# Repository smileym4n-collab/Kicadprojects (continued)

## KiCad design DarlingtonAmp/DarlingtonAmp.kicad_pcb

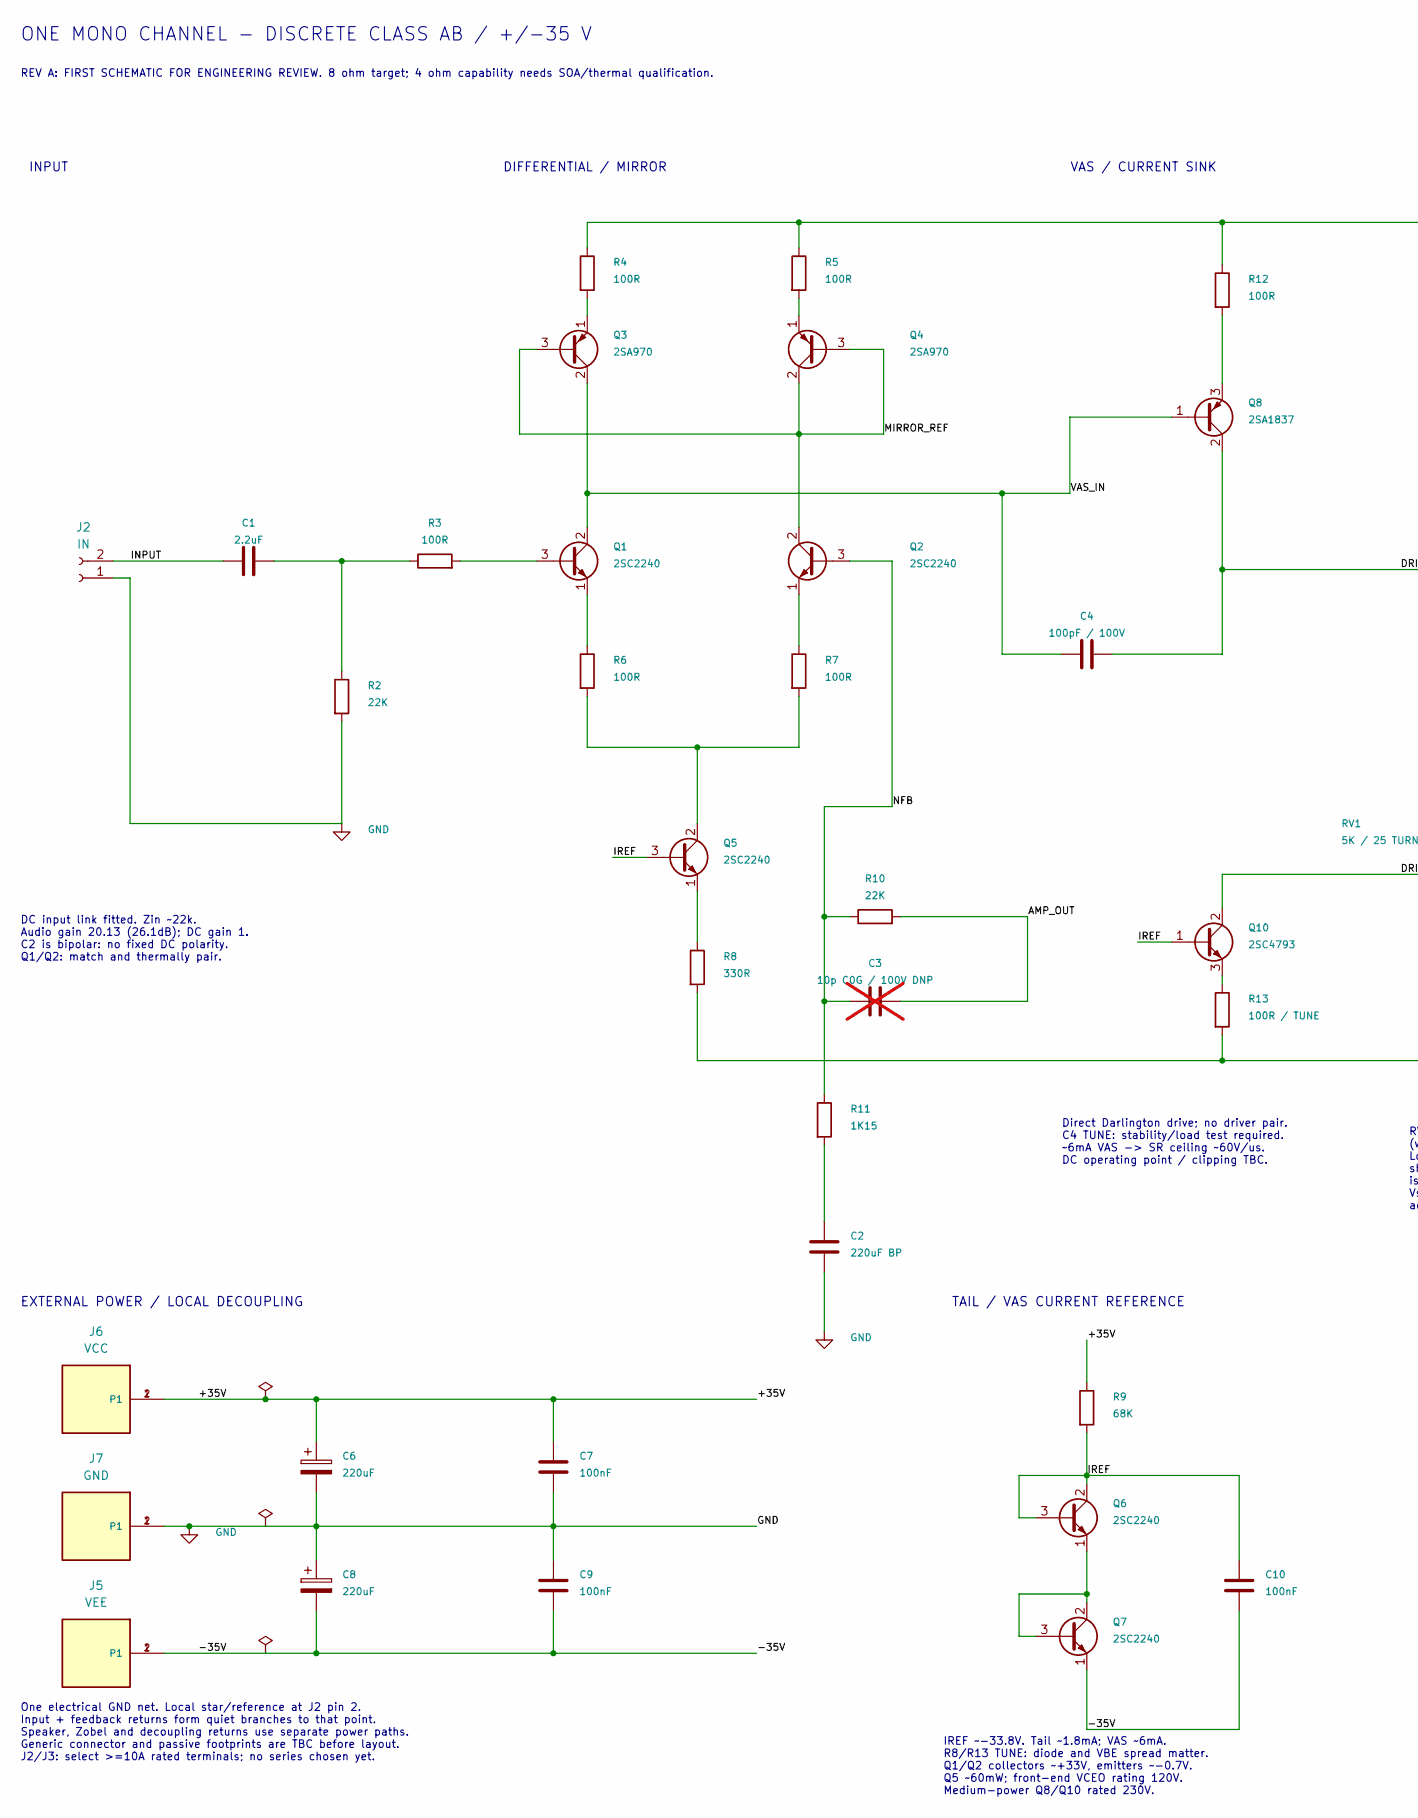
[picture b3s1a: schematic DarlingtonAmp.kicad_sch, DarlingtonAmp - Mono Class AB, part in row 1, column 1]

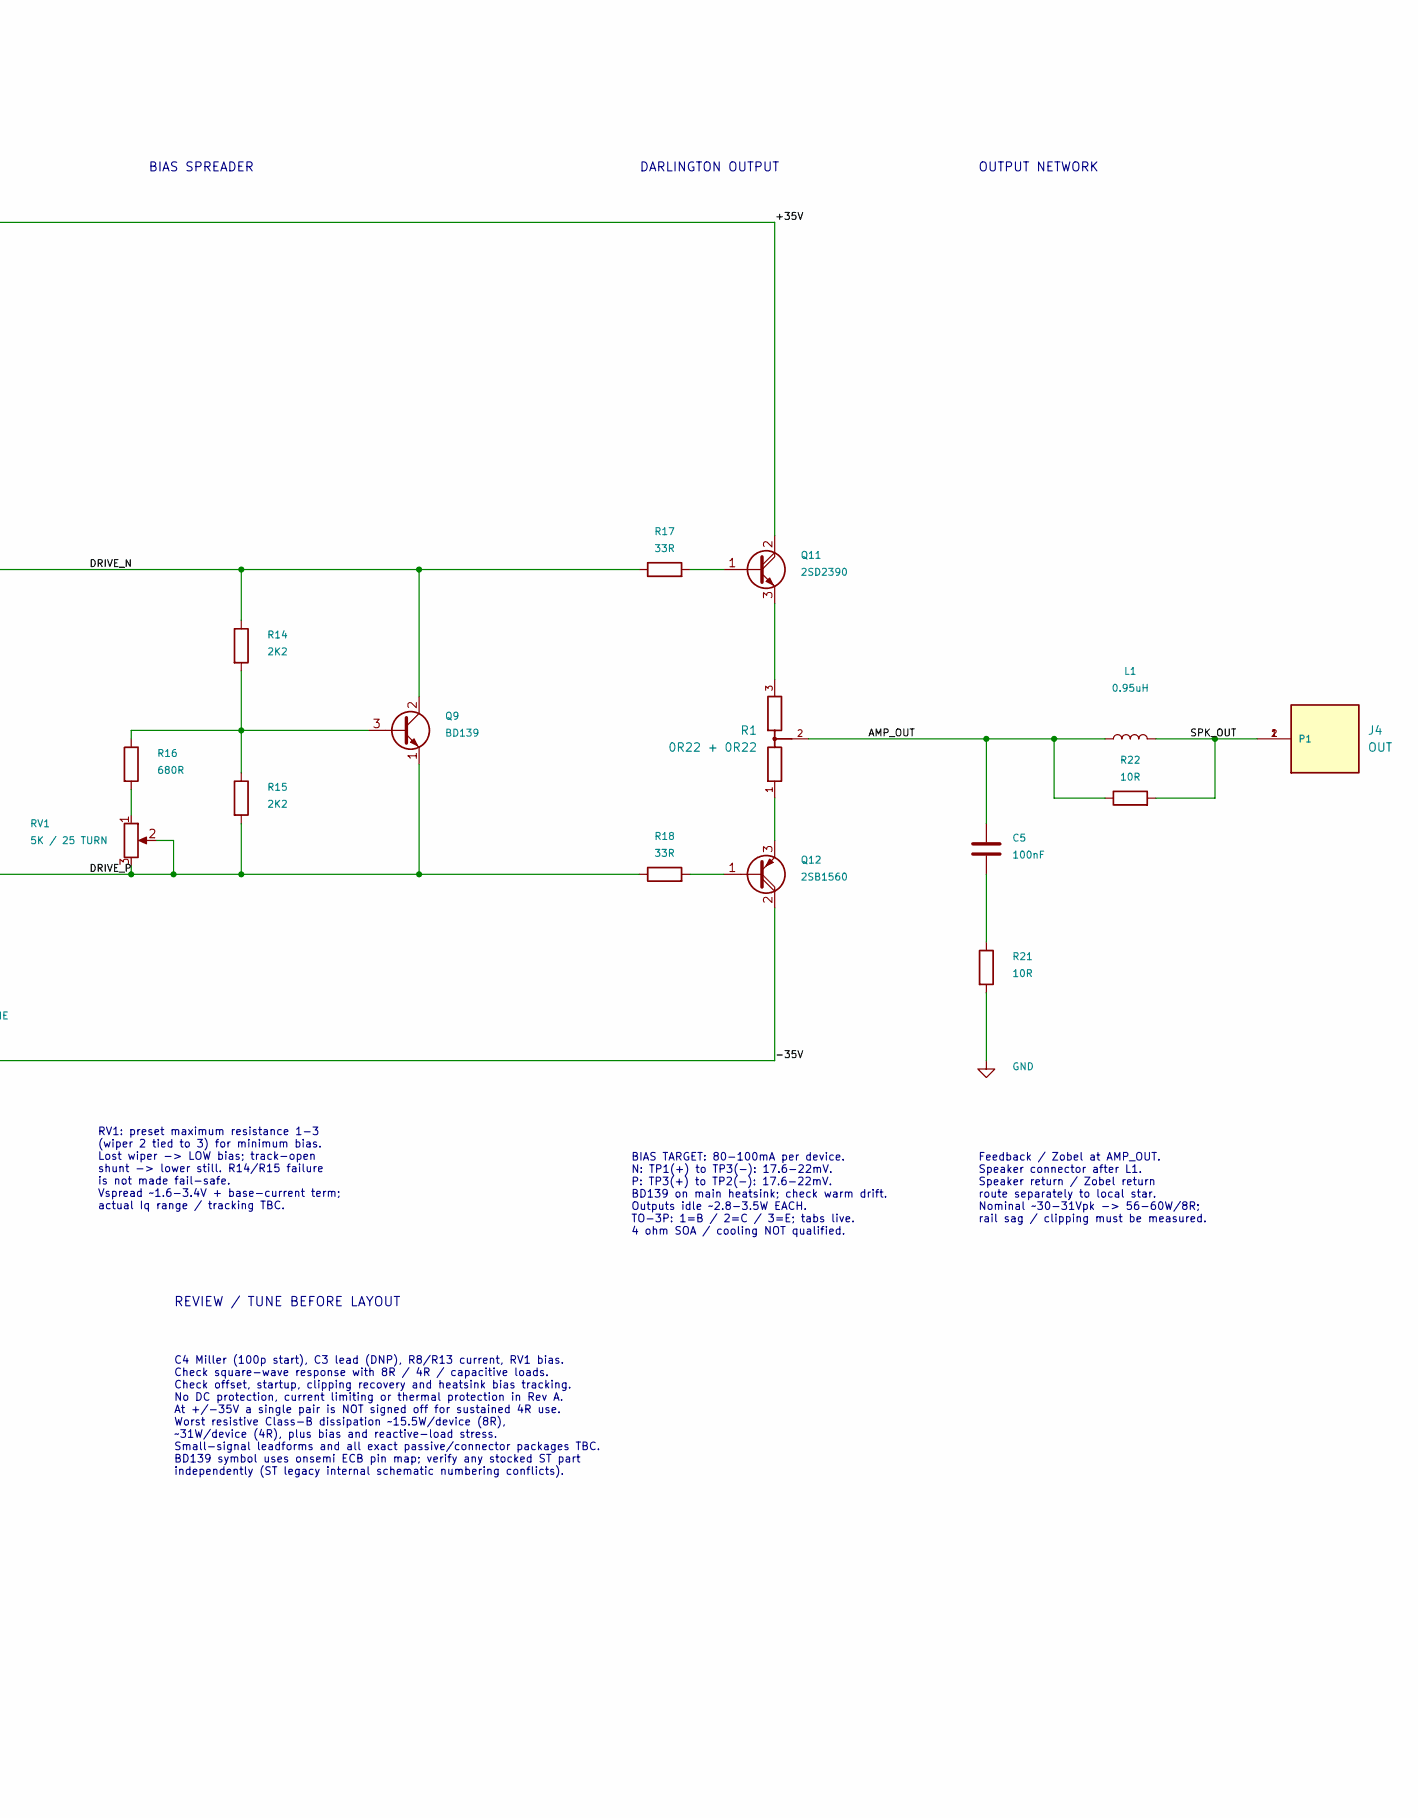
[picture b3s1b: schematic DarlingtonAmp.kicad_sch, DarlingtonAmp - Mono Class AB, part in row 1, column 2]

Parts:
C1: 2.2uF; C_Rect_L7.2mm_W7.2mm_P5.00mm_FKS2_FKP2_MKS2_MKP2
C2: 220uF BP; C_Radial_D16.0mm_H25.0mm_P7.50mm
C3: 10p C0G / 100V DNP; C_Disc_D4.3mm_W1.9mm_P5.00mm; not fitted
C4: 100pF / 100V; C_0805_2012Metric_Pad1.18x1.45mm_HandSolder
C5, C7, C9, C10: 100nF; C_Rect_L7.0mm_W2.5mm_P5.00mm
C6, C8: 220uF; CP_Radial_D10.0mm_P5.00mm
J2: IN; JST_XH_B2B-XH-A_1x02_P2.50mm_Vertical
J4: OUT; TE_62409-1; PART_DESCRIPTION CONN QC TAB 0.250 SOLDER
J5: VEE; TE_62409-1; PART_DESCRIPTION CONN QC TAB 0.250 SOLDER
J6: VCC; TE_62409-1; PART_DESCRIPTION CONN QC TAB 0.250 SOLDER
J7: GND; TE_62409-1; PART_DESCRIPTION CONN QC TAB 0.250 SOLDER
L1: 0.95uH; L_Yamaha_L505_15x15mm_P12mm
Q1, Q2, Q5, Q6, Q7: 2SC2240; TO-92_Inline_Wide
Q3, Q4: 2SA970; TO-92_Inline_Wide
Q8: 2SA1837; TO-220-3_Vertical
Q9: BD139; TO-126-3_Horizontal_TabDown
Q10: 2SC4793; TO-220-3_Vertical
Q11: 2SD2390; TO-3PB-3_Horizontal_TabDown
Q12: 2SB1560; TO-3PB-3_Horizontal_TabDown
R1: 0R22 + 0R22; R_Dual_Power_L31_W5_H18_P10
R2, R10: 22K; R_Axial_DIN0207_L6.3mm_D2.5mm_P7.62mm_Horizontal
R3, R4, R5, R6, R7, R12: 100R; R_Axial_DIN0207_L6.3mm_D2.5mm_P7.62mm_Horizontal
R8: 330R; R_Axial_DIN0207_L6.3mm_D2.5mm_P7.62mm_Horizontal
R9: 68K; R_Axial_DIN0207_L6.3mm_D2.5mm_P7.62mm_Horizontal
R11: 1K15; R_Axial_DIN0207_L6.3mm_D2.5mm_P7.62mm_Horizontal
R13: 100R / TUNE; R_Axial_DIN0207_L6.3mm_D2.5mm_P7.62mm_Horizontal
R14, R15: 2K2; R_Axial_DIN0207_L6.3mm_D2.5mm_P7.62mm_Horizontal
R16: 680R; R_Axial_DIN0207_L6.3mm_D2.5mm_P7.62mm_Horizontal
R17, R18: 33R; R_Axial_DIN0207_L6.3mm_D2.5mm_P7.62mm_Horizontal
R21, R22: 10R; R_Axial_DIN0414_L11.9mm_D4.5mm_P15.24mm_Horizontal
RV1: 5K / 25 TURN; Potentiometer_Bourns_3296W_Vertical

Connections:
/+35V: C6.1, C7.1, J6.1, J6.2 (P1), Q11.2 (C), R4.1, R5.1, R9.1, R12.1
/-35V: C8.2, C9.2, C10.2, J5.1, J5.2 (P1), Q7.1 (E), Q12.2 (C), R8.2, R13.2
/AMP_OUT: C3.2, C5.1, L1.1, R1.2 (COM), R10.2, R22.1
/DRIVE_N: C4.2, Q8.2 (C), Q9.2 (C), R14.1, R17.1
/DRIVE_P: Q9.1 (E), Q10.2 (C), R15.2, R18.1, RV1.2, RV1.3
/INPUT: C1.1, J2.2
/IREF: C10.1, Q5.3 (B), Q6.2 (C), Q6.3 (B), Q10.1 (B), R9.2
/MIRROR_REF: Q2.2 (C), Q3.3 (B), Q4.2 (C), Q4.3 (B)
/NFB: C3.1, Q2.3 (B), R10.1, R11.1
/SPK_OUT: J4.1, J4.2 (P1), L1.2, R22.2
/VAS_IN: C4.1, Q1.2 (C), Q3.2 (C), Q8.1 (B)
GND: C2.2, C6.2, C7.2, C8.1, C9.1, J2.1, J7.1, J7.2 (P1), R2.2, R21.2
unnamed: C1.2, R2.1, R3.1
unnamed: C2.1, R11.2
unnamed: C5.2, R21.1
unnamed: Q1.3 (B), R3.2
unnamed: Q1.1 (E), R6.1
unnamed: Q2.1 (E), R7.1
unnamed: Q3.1 (E), R4.2
unnamed: Q4.1 (E), R5.2
unnamed: Q5.2 (C), R6.2, R7.2
unnamed: Q5.1 (E), R8.1
unnamed: Q6.1 (E), Q7.2 (C), Q7.3 (B)
unnamed: Q8.3 (E), R12.2
unnamed: Q9.3 (B), R14.2, R15.1, R16.1
unnamed: Q10.3 (E), R13.1
unnamed: Q11.1 (B), R17.2
unnamed: Q11.3 (E), R1.3 (B)
unnamed: Q12.1 (B), R18.2
unnamed: Q12.3 (E), R1.1 (A)
unnamed: R16.2, RV1.1

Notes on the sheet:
VAS / CURRENT SINK
Direct Darlington drive; no driver pair. C4 TUNE: stability/load test required. ~6mA VAS -> SR ceiling ~60V/us. DC operating point / clipping TBC.
OUTPUT NETWORK
C4 Miller (100p start), C3 lead (DNP), R8/R13 current, RV1 bias. Check square-wave response with 8R / 4R / capacitive loads. Check offset, startup, clipping recovery and heatsink bias tracking. No DC protection, current limiting or thermal protection in Rev A. At +/-35V a single pair is NOT signed 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
INPUT
IREF ~-33.8V. Tail ~1.8mA; VAS ~6mA. R8/R13 TUNE: diode and VBE spread matter. Q1/Q2 collectors ~+33V, emitters ~-0.7V. Q5 ~60mW; front-end VCEO rating 120V. Medium-power Q8/Q10 rated 230V.
BIAS SPREADER
ONE MONO CHANNEL - DISCRETE CLASS AB / +/-35 V
One electrical GND net. Local star/reference at J2 pin 2. Input + feedback returns form quiet branches to that point. Speaker, Zobel and decoupling returns use separate power paths. Generic connector and passive footprints are TBC before layout. J2/J3: select >=10A rated terminals; no series chosen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
Feedback / Zobel at AMP_OUT. Speaker connector after L1. Speaker return / Zobel return route separately to local star. Nominal ~30-31Vpk -> 56-60W/8R; rail sag / clipping must be measured.
EXTERNAL POWER / LOCAL DECOUPLING
BIAS TARGET: 80-100mA per device. N: TP1(+) to TP3(-): 17.6-22mV. P: TP3(+) to TP2(-): 17.6-22mV. BD139 on main heatsink; check warm drift. Outputs idle ~2.8-3.5W EACH. TO-3P: 1=B / 2=C / 3=E; tabs live. 4 ohm SOA / cooling NOT qualified.
DC input link fitted. Zin ~22k. Audio gain 20.13 (26.1dB); DC gain 1. C2 is bipolar: no fixed DC polarity. Q1/Q2: match and thermally pair.
DIFFERENTIAL / MIRROR
REV A: FIRST SCHEMATIC FOR ENGINEERING REVIEW. 8 ohm target; 4 ohm capability needs SOA/thermal qualification.
TAIL / VAS CURRENT REFERENCE
REVIEW / TUNE BEFORE LAYOUT
DARLINGTON OUTPUT
RV1: preset maximum resistance 1-3 (wiper 2 tied to 3) for minimum bias. Lost wiper -> LOW bias; track-open shunt -> lower still. R14/R15 failure is not made fail-safe. Vspread ~1.6-3.4V + base-current term; actual Iq range / tracking TBC.

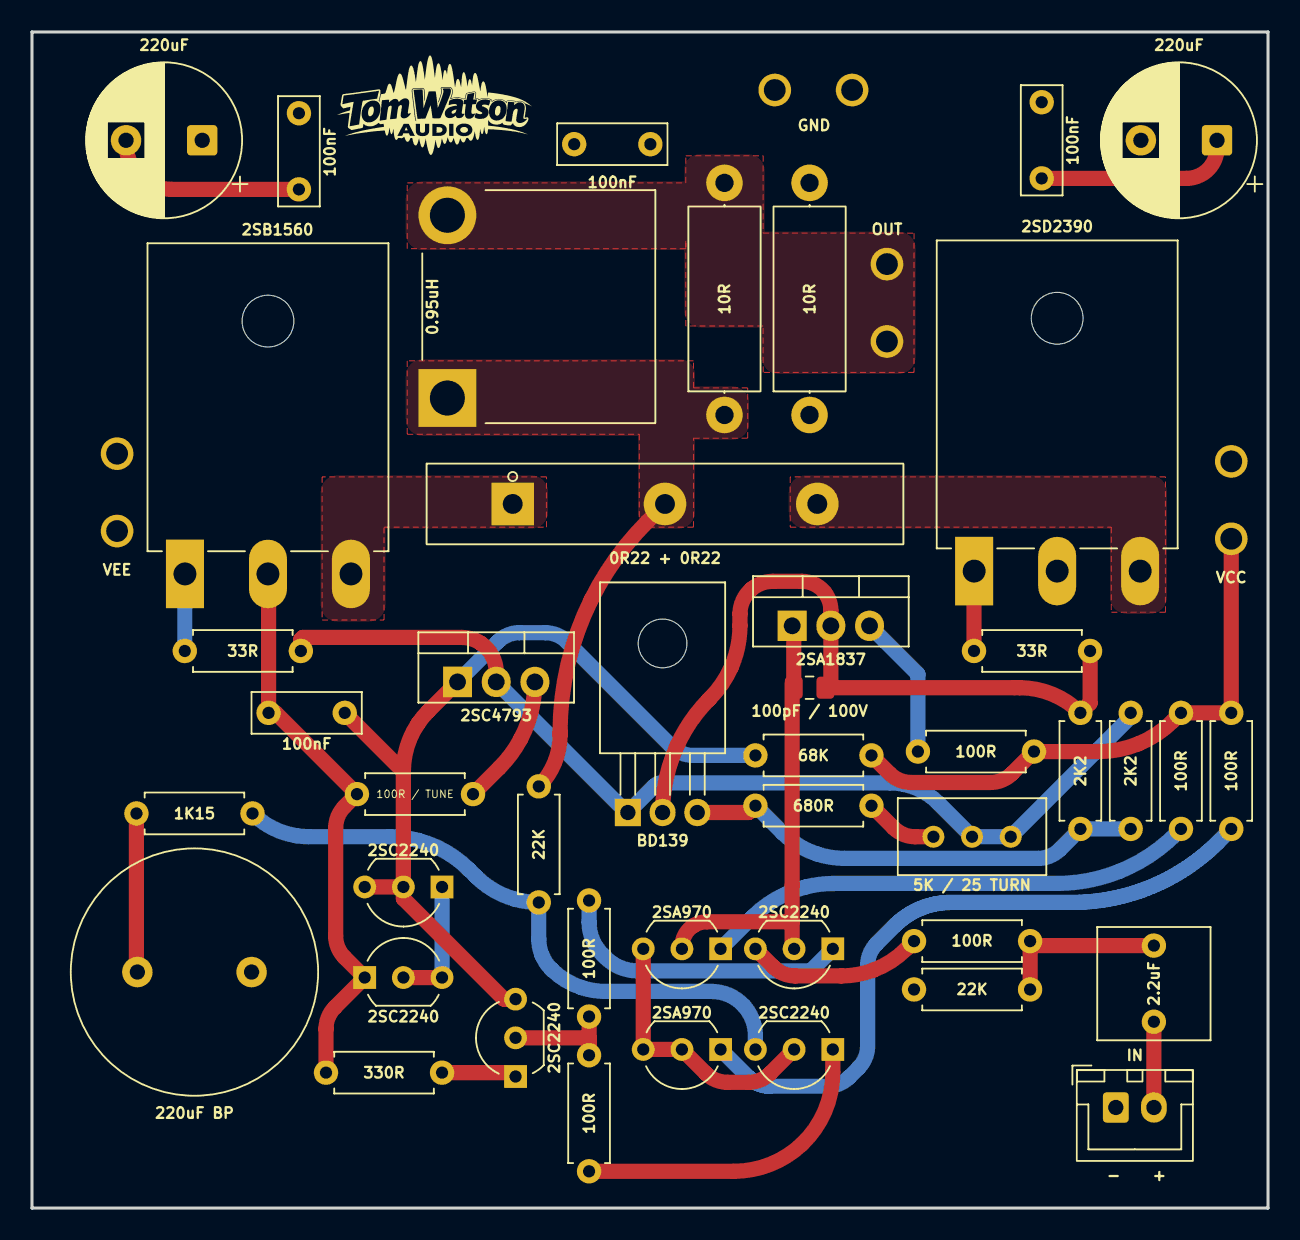
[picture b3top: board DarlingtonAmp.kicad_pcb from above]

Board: 2 copper layers, 81.2 x 77.2 mm, 48 parts (0 on the bottom side), 31 nets.
